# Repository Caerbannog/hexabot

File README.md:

Hexabot Sources
===============

Design files and source code of a mobile robot for the [Eurobot competition](http://www.eurobot.org/).

The controller board is built in [KiCad](http://www.kicad.org/)
around a [dsPIC33EP256MU806](https://www.microchip.com/products/dsPIC33EP256MU806) (QFN, motor control, USB).
You can control it from your development machine or an embedded Linux like the Raspberry Pi (raspbian jessie recommended).

Controller PCB
--------------
The board handles various functions: motor control, odometry, sensors and servomotors.
It has two layers, 10cm*10cm and mostly 0806 SMT components.

You can buy 10 PCBs for 32$ at [SeeedStudio](http://www.seeedstudio.com/service/index.php?r=pcb).
Then we hand-soldered ours.

Embedded Software
-----------------
The source code for the microcontroller is in [hexabot-dsPIC33.X](hexabot-dsPIC33.X/).
It is controlled with the tools in [linux](linux/). Most are Python scripts that
use [PyUSB](https://walac.github.io/pyusb/) to communicate with the board through independant USB endpoints:
- Bulk commands to set parameters and read back values. The basic idea is to run `./command.py <register> <value>` to set a value.
- Bulk metrics broadcasting, isochronous packets for time-sensitive data. Dump them with `./usb_controller.py`.
- Serial port for debugging. Show the debug console with `miniterm.py /dev/ttyACM* 9600 -D`.

A higher level scripts like `joystick.py` uses the command endpoint to let you control the motors with a USB joystick.

User Interface
--------------
The [ui](ui/) directory contains a Python webserver with these features:
- live updates of the position according to odometry,
- graphs to visualize metrics,
- maybe someday a way to send commands.

Setup
-----
Download and install the [MPLABX IDE](http://www.microchip.com/mplabx/) and the [XC16 compiler](http://www.microchip.com/compilers/).
You need xc16 v1.25+ because of bug XC16-781 (snprintf).
Sadly the peripheral libraries were last shipped with v1.24 and the new Code Configurator doesn't support dsPIC33E yet.
You need to copy the libraries from one installed version to the other.

Install Python 3 and debugging tools like Wireshark.
For Ubuntu 15.04 you can run:
```bash
git clone https://github.com/Caerbannog/hexabot.git
sudo apt-get install python3-pip wireshark
sudo pip3 install pyusb==1.0.0b1 autobahn==0.10.4 pyinotify==0.9.6 bottle==0.12.8 pyserial
sudo adduser $USER dialout
sudo adduser $USER wireshark
echo usbmon | sudo tee -a /etc/modules
sudo cp 99-hexabot.rules /etc/udev/rules.d/
sudo service udev reload # then you need to replug the device
```

Contributing
------------
Pull requests are welcome on the project page:
<https://github.com/Caerbannog/hexabot>

Licenses
--------
- Hardware design files are published under the CERN OHL v.1.2.
- Source code is published under the GPLv3 or later.
- Note that Microchip's USB library and the CDC-basic demo have a more restrictive license.

TODO list
---------
- Documentation for the code. Links to documentation for the motor control and odometry.

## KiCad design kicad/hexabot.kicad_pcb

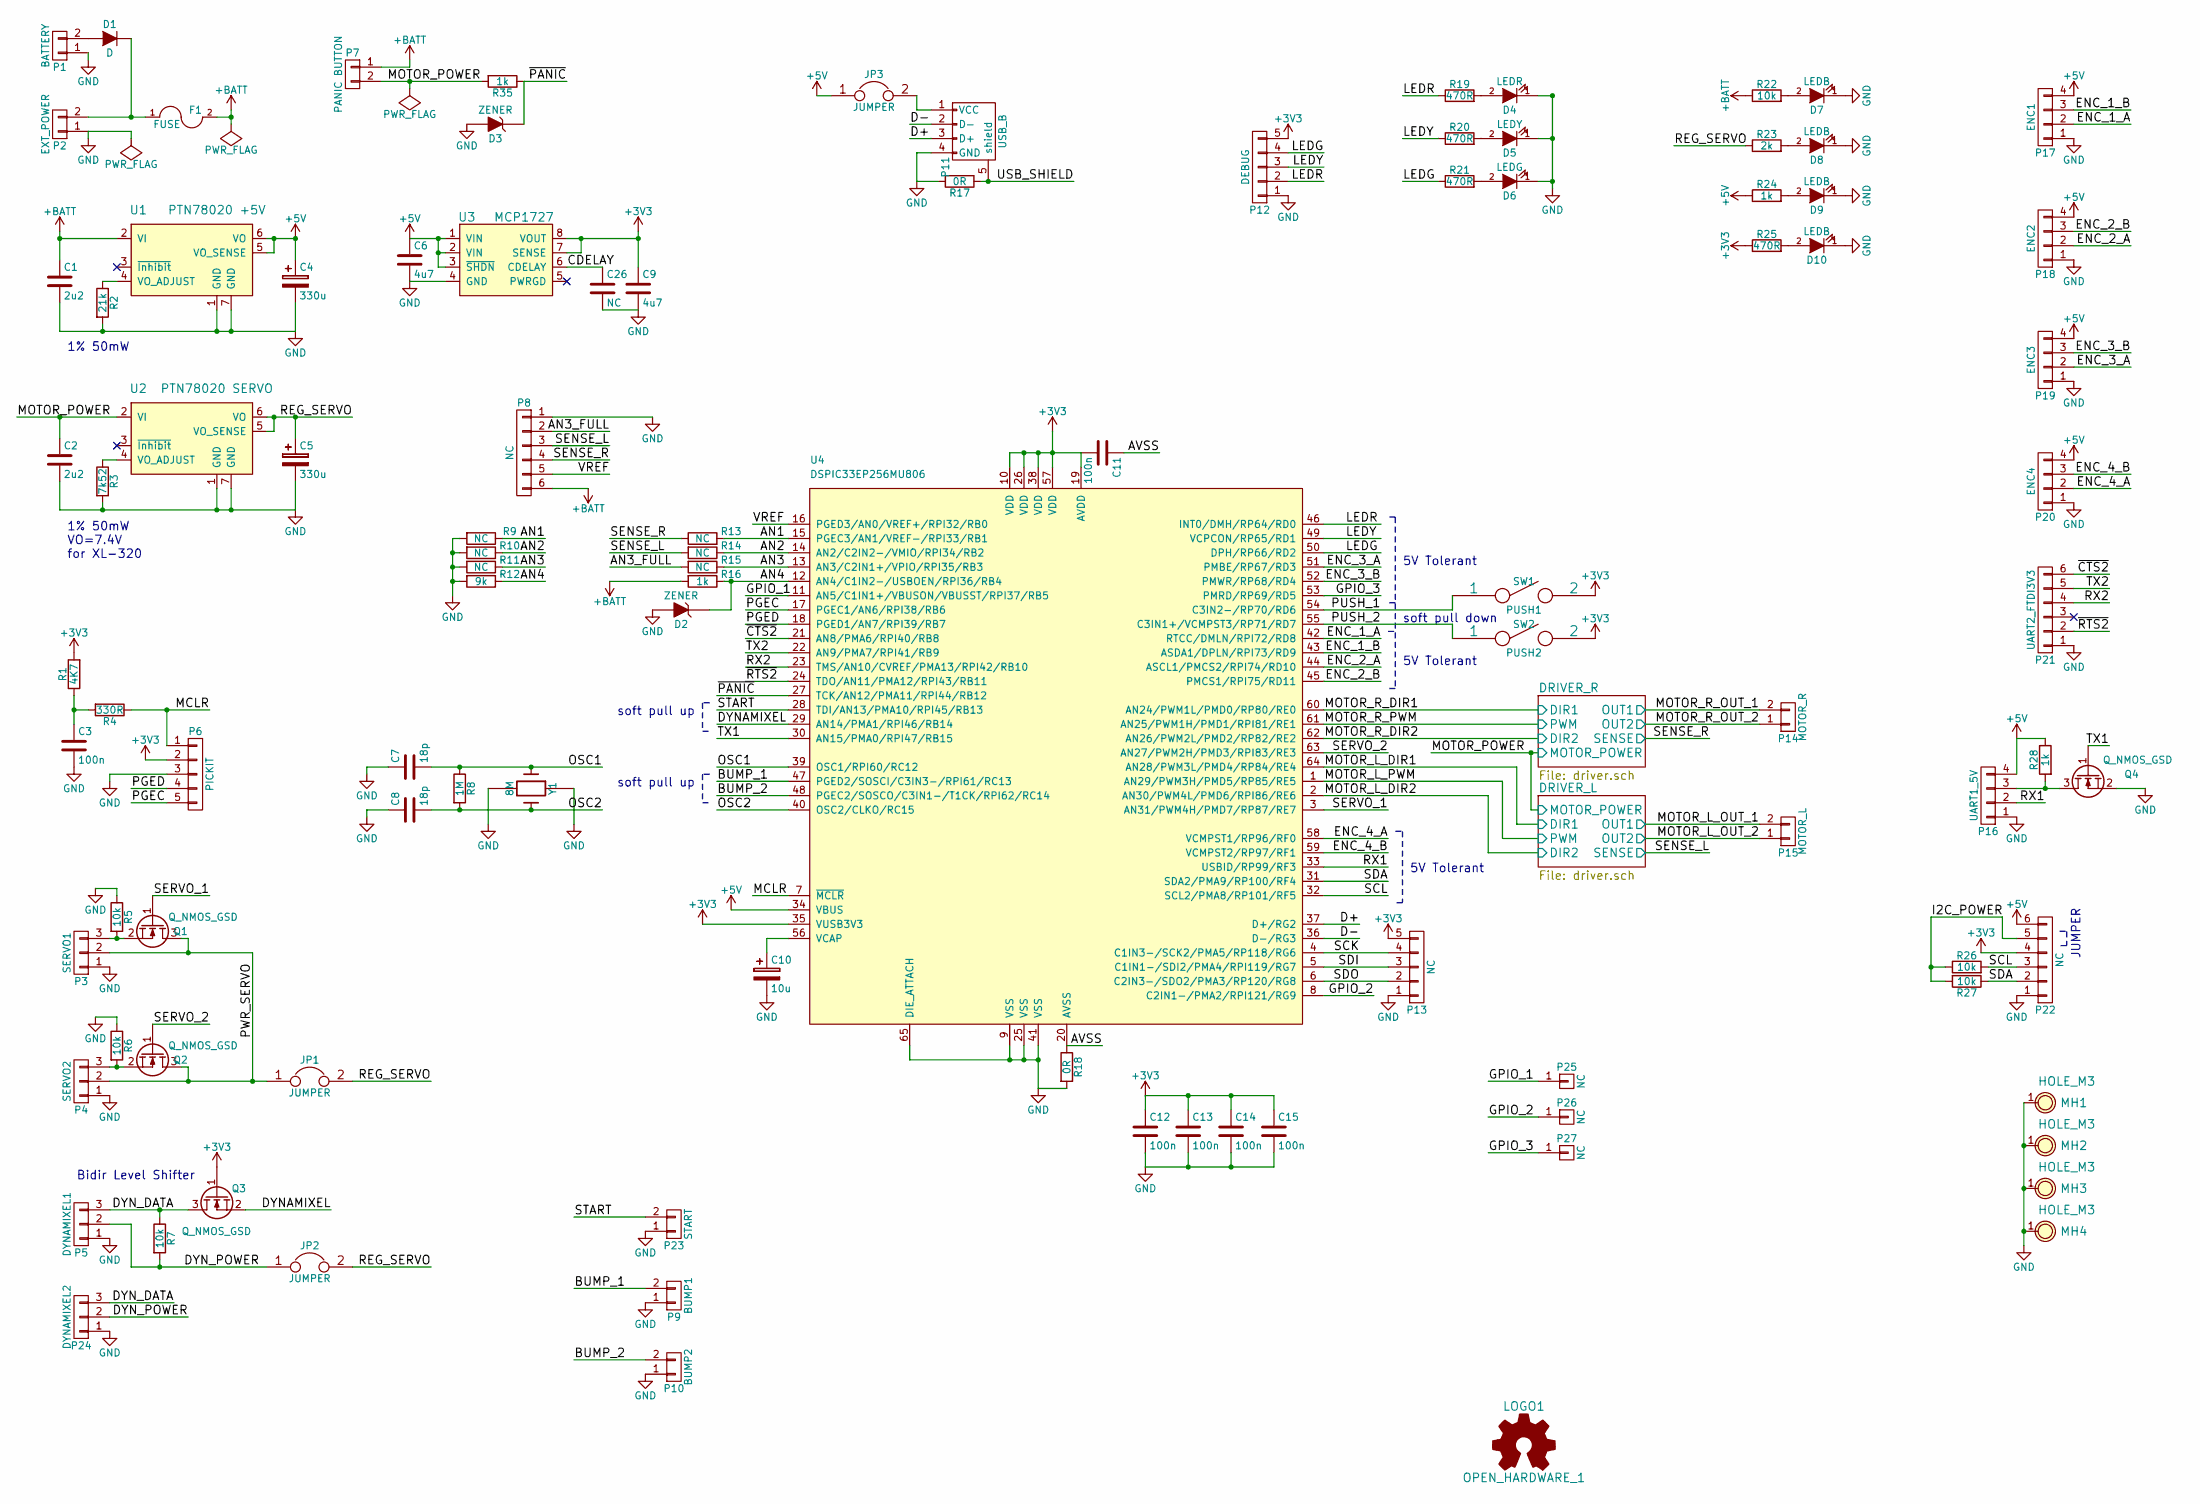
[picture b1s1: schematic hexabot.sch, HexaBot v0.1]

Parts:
C1, C2: 2u2; R_0805
C3, C11, C12, C13, C14, C15: 100n; R_0805
C4: 330u; c_elec_8x10.5
C5: 330u; c_elec_10x10.5
C6, C9: 4u7; R_0805
C7, C8: 18p; R_0805
C10: 10u; R_0805
C26: NC; R_0805
D1: D; SOD-128
D2, D3: ZENER; SOD-323
D4: LEDR; R_0805
D5: LEDY; R_0805
D6: LEDG; R_0805
D7, D8, D9, D10: LEDB; R_0805
F1: FUSE; R_1206_HandSoldering
JP1, JP2, JP3: JUMPER; Pin_Header_Straight_1x02
LOGO1: OPEN_HARDWARE_1; Symbol_OSHW-Logo_SilkScreen
MH1, MH2, MH3, MH4: HOLE_M3; M3-hole-plated
P1: BATTERY; Socket_MOLEX-KK-RM3-96mm_Lock_2pin_straight
P2: EXT_POWER; Socket_MOLEX-KK-RM3-96mm_Lock_2pin_straight
P3: SERVO1; Pin_Header_Straight_1x03
P4: SERVO2; Pin_Header_Straight_1x03
P5: DYNAMIXEL1; molex-22-03-5035
P6: PICKIT; Pin_Header_Straight_1x05
P7: PANIC BUTTON; Socket_MOLEX-KK-RM3-96mm_Lock_2pin_straight
P8: NC; Pin_Header_Straight_1x06
P9: BUMP1; Socket_MOLEX-KK-RM2-54mm_Lock_2pin_straight
P10: BUMP2; Socket_MOLEX-KK-RM2-54mm_Lock_2pin_straight
P11: USB_B; MICRO-B_USB
P12: DEBUG; Socket_MOLEX-KK-RM2-54mm_Lock_5pin_straight
P13: NC; Socket_MOLEX-KK-RM2-54mm_Lock_5pin_straight
P14: MOTOR_R; Socket_MOLEX-KK-RM3-96mm_Lock_2pin_straight
P15: MOTOR_L; Socket_MOLEX-KK-RM3-96mm_Lock_2pin_straight
P16: UART1_5V; Socket_MOLEX-KK-RM2-54mm_Lock_4pin_straight
P17: ENC1; Socket_MOLEX-KK-RM2-54mm_Lock_4pin_straight
P18: ENC2; Socket_MOLEX-KK-RM2-54mm_Lock_4pin_straight
P19: ENC3; Socket_MOLEX-KK-RM2-54mm_Lock_4pin_straight
P20: ENC4; Socket_MOLEX-KK-RM2-54mm_Lock_4pin_straight
P21: UART2_FTDI3V3; Pin_Header_Straight_1x06
P22: NC; Socket_MOLEX-KK-RM2-54mm_Lock_6pin_straight
P23: START; Socket_MOLEX-KK-RM2-54mm_Lock_2pin_straight
P24: DYNAMIXEL2; molex-22-03-5035
P25, P26, P27: NC; Pin_Header_Straight_1x01
Q1, Q2, Q3, Q4: Q_NMOS_GSD; SOT-23
R1: 4K7; R_0805
R2: 21k; R_0805
R3: 7k52; R_0805
R4: 330R; R_0805
R5, R6, R7, R22, R26, R27: 10k; R_0805
R8: 1M; R_0805
R9, R10, R11, R13, R14, R15: NC; R_0805
R12: 9k; R_0805
R16, R24, R28, R35: 1k; R_0805
R17, R18: 0R; R_0805
R19, R20, R21, R25: 470R; R_0805
R23: 2k; R_0805
SW1: PUSH1; SW_PUSH-SMD
SW2: PUSH2; SW_PUSH-SMD
U1: PTN78020 +5V; PTN78020H
U2: PTN78020 SERVO; PTN78020H
U3: MCP1727; SOIC-8_3.9x4.9mm_Pitch1.27mm
U4: DSPIC33EP256MU806; QFN-64-1EP_9x9mm_Pitch0.5mm
Y1: 8M; XTAL_5x3.2

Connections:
+3V3: C9.1, C11.2, C12.1, C13.1, C14.1, C15.1, P6.2, P12.5, P13.5, P22.4, Q3.1 (G), R1.2, R25.1, SW1.2, SW2.2, U3.7 (SENSE), U3.8 (VOUT), U4.10 (VDD), U4.19 (AVDD), U4.26 (VDD), U4.35 (VUSB3V3), U4.38 (VDD), U4.57 (VDD)
+5V: C4.1, C6.1, JP3.1, P16.4, P17.4, P18.4, P19.4, P20.4, P22.6, R24.1, R28.1, U1.5 (VO_SENSE), U1.6 (VO), U3.1 (VIN), U3.2 (VIN), U3.3 (~SHDN), U4.34 (VBUS)
+BATT: C1.1, F1.2, P7.1, P8.6, R16.2, R22.1, U1.2 (VI)
/AN1: R9.1, R13.2, U4.15 (PGEC3/AN1/VREF-/RPI33/RB1)
/AN2: R10.1, R14.1, U4.14 (AN2/C2IN2-/VMIO/RPI34/RB2)
/AN3: R11.1, R15.1, U4.13 (AN3/C2IN1+/VPIO/RPI35/RB3)
/AN3_FULL: P8.2, R15.2
/AN4: D2.1 (K), R12.1, R16.1, U4.12 (AN4/C1IN2-/USBOEN/RPI36/RB4)
/AVSS: C11.1, R18.1, U4.20 (AVSS)
/BUMP_1: P9.2, U4.47 (PGED2/SOSCI/C3IN3-/RPI61/RC13)
/BUMP_2: P10.2, U4.48 (PGEC2/SOSCO/C3IN1-/T1CK/RPI62/RC14)
/CDELAY: C26.1, U3.6 (CDELAY)
/D+: P11.3 (D+), U4.37 (D+/RG2)
/D-: P11.2 (D-), U4.36 (D-/RG3)
/DRIVER_L/DIR1: U4.64 (AN28/PWM3L/PMD4/RP84/RE4); also elsewhere on the board
/DRIVER_L/DIR2: U4.2 (AN30/PWM4L/PMD6/RPI86/RE6); also elsewhere on the board
/DRIVER_L/MOTOR_POWER: C2.1, P7.2, R35.2, U2.2 (VI); also elsewhere on the board
/DRIVER_L/OUT1: P15.2; also elsewhere on the board
/DRIVER_L/OUT2: P15.1; also elsewhere on the board
/DRIVER_L/PWM: U4.1 (AN29/PWM3H/PMD5/RP85/RE5); also elsewhere on the board
/DRIVER_L/SENSE: P8.3, R14.2; also elsewhere on the board
/DRIVER_R/DIR1: U4.60 (AN24/PWM1L/PMD0/RP80/RE0); also elsewhere on the board
/DRIVER_R/DIR2: U4.62 (AN26/PWM2L/PMD2/RP82/RE2); also elsewhere on the board
/DRIVER_R/OUT1: P14.2; also elsewhere on the board
/DRIVER_R/OUT2: P14.1; also elsewhere on the board
/DRIVER_R/PWM: U4.61 (AN25/PWM1H/PMD1/RPI81/RE1); also elsewhere on the board
/DRIVER_R/SENSE: P8.4, R13.1; also elsewhere on the board
/DYNAMIXEL: Q3.2 (S), U4.29 (AN14/PMA1/RPI46/RB14)
/DYN_DATA: P5.3, P24.3, Q3.3 (D), R7.1
/DYN_POWER: JP2.1, P5.2, P24.2, R7.2
/ENC_1_A: P17.2, U4.42 (RTCC/DMLN/RPI72/RD8)
/ENC_1_B: P17.3, U4.43 (ASDA1/DPLN/RPI73/RD9)
/ENC_2_A: P18.2, U4.44 (ASCL1/PMCS2/RPI74/RD10)
/ENC_2_B: P18.3, U4.45 (PMCS1/RPI75/RD11)
/ENC_3_A: P19.2, U4.51 (PMBE/RP67/RD3)
/ENC_3_B: P19.3, U4.52 (PMWR/RP68/RD4)
/ENC_4_A: P20.2, U4.58 (VCMPST1/RP96/RF0)
/ENC_4_B: P20.3, U4.59 (VCMPST2/RP97/RF1)
/GPIO_1: P25.1, U4.11 (AN5/C1IN1+/VBUSON/VBUSST/RPI37/RB5)
/GPIO_2: P26.1, U4.8 (C2IN1-/PMA2/RPI121/RG9)
/GPIO_3: P27.1, U4.53 (PMRD/RP69/RD5)
/I2C_POWER: P22.5, R26.1, R27.2
/LEDG: P12.4, R21.1, U4.50 (DPH/RP66/RD2)
/LEDR: P12.2, R19.1, U4.46 (INT0/DMH/RP64/RD0)
/LEDY: P12.3, R20.1, U4.49 (VCPCON/RP65/RD1)
/MCLR: P6.1, R4.1, U4.7 (~MCLR)
/OSC1: C7.2, R8.1, U4.39 (OSC1/RPI60/RC12), Y1.1
/OSC2: C8.2, R8.2, U4.40 (OSC2/CLKO/RC15), Y1.2
/PGEC: P6.5, U4.17 (PGEC1/AN6/RPI38/RB6)
/PGED: P6.4, U4.18 (PGED1/AN7/RPI39/RB7)
/PUSH_1: SW1.1, U4.54 (C3IN2-/RP70/RD6)
/PUSH_2: SW2.1, U4.55 (C3IN1+/VCMPST3/RP71/RD7)
/PWR_SERVO: JP1.1, P3.2, P4.2, Q1.3 (D), Q2.3 (D)
/REG_SERVO: C5.1, JP1.2, JP2.2, R23.1, U2.5 (VO_SENSE), U2.6 (VO)
/RX1: P16.2, U4.33 (USBID/RP99/RF3)
/RX2: P21.4, U4.23 (TMS/AN10/CVREF/PMA13/RPI42/RB10)
/SCK: P13.4, U4.4 (C1IN3-/SCK2/PMA5/RP118/RG6)
/SCL: P22.3, R26.2, U4.32 (SCL2/PMA8/RP101/RF5)
/SDA: P22.2, R27.1, U4.31 (SDA2/PMA9/RP100/RF4)
/SDI: P13.3, U4.5 (C1IN1-/SDI2/PMA4/RPI119/RG7)
/SDO: P13.2, U4.6 (C2IN3-/SDO2/PMA3/RP120/RG8)
/SERVO_1: Q1.1 (G), U4.3 (AN31/PWM4H/PMD7/RP87/RE7)
/SERVO_2: Q2.1 (G), U4.63 (AN27/PWM2H/PMD3/RPI83/RE3)
/START: P23.2, U4.28 (TDI/AN13/PMA10/RPI45/RB13)
/TX1: Q4.1 (G), U4.30 (AN15/PMA0/RPI47/RB15)
/TX2: P21.5, U4.22 (AN9/PMA7/RPI41/RB9)
/USB_SHIELD: P11.5 (shield), R17.1
/VREF: P8.5, U4.16 (PGED3/AN0/VREF+/RPI32/RB0)
/~CTS2: P21.6, U4.21 (AN8/PMA6/RPI40/RB8)
/~PANIC: D3.1 (K), R35.1, U4.27 (TCK/AN12/PMA11/RPI44/RB12)
/~RTS2: P21.2, U4.24 (TDO/AN11/PMA12/RPI43/RB11)
GND: C1.2, C2.2, C3.2, C4.2, C5.2, C6.2, C7.1, C8.1, C9.2, C10.2, C12.2, C13.2, C14.2, C15.2, C26.2, D2.2 (A), D3.2 (A), D4.1 (K), D5.1 (K), D6.1 (K), D7.1 (K), D8.1 (K), D9.1 (K), D10.1 (K), MH1.1, MH2.1, MH3.1, MH4.1, P1.1, P2.1, P3.1, P4.1, P5.1, P6.3, P8.1, P9.1, P10.1, P11.4 (GND), P12.1, P13.1, P16.1, P17.1, P18.1, P19.1, P20.1, P21.1, P22.1, P23.1, P24.1, Q4.2 (S), R2.2, R3.2, R5.1, R6.1, R9.2, R10.2, R11.2, R12.2, R17.2, R18.2, U1.1 (GND), U1.7 (GND), U2.1 (GND), U2.7 (GND), U3.4 (GND), U4.9 (VSS), U4.25 (VSS), U4.41 (VSS), U4.65 (DIE_ATTACH), Y1.3 (GND), Y1.4 (GND); also elsewhere on the board
unnamed: C3.1, R1.1, R4.2
unnamed: C10.1, U4.56 (VCAP)
unnamed: D1.1 (K), F1.1, P2.2
unnamed: D1.2 (A), P1.2
unnamed: D4.2 (A), R19.2
unnamed: D5.2 (A), R20.2
unnamed: D6.2 (A), R21.2
unnamed: D7.2 (A), R22.2
unnamed: D8.2 (A), R23.2
unnamed: D9.2 (A), R24.2
unnamed: D10.2 (A), R25.2
unnamed: JP3.2, P11.1 (VCC)
unnamed: P3.3, Q1.2 (S), R5.2
unnamed: P4.3, Q2.2 (S), R6.2
unnamed: P16.3, Q4.3 (D), R28.2
unnamed: R2.1, U1.4 (VO_ADJUST)
unnamed: R3.1, U2.4 (VO_ADJUST)

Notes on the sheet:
5V Tolerant
1% 50mW
1% 50mW VO=7.4V for XL-320
soft pull down
JUMPER
soft pull up
Bidir Level Shifter

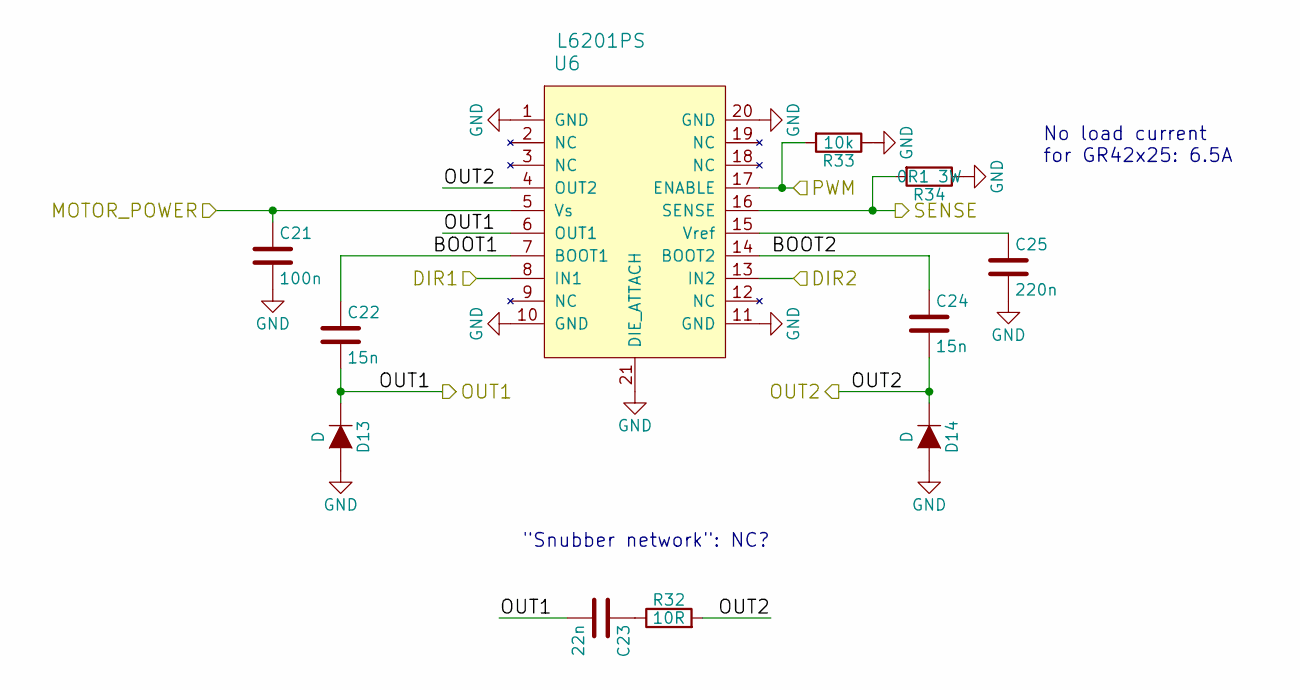
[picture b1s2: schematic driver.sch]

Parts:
C16: 100n; R_0805
C17, C19: 15n; R_0805
C18: 22n; R_0805
C20: 220n; R_0805
D11, D12: D; SOD-123
R29: 10R; R_0805
R30: 10k; R_0805
R31: 0R1 3W; R_1206
U5: L6201PS; powerso-20

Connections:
/DRIVER_L/MOTOR_POWER: C16.1, U5.5 (Vs); also elsewhere on the board
/DRIVER_R/BOOT1: C17.1, U5.7 (BOOT1)
/DRIVER_R/BOOT2: C19.1, U5.14 (BOOT2)
/DRIVER_R/DIR1: U5.8 (IN1); also elsewhere on the board
/DRIVER_R/DIR2: U5.13 (IN2); also elsewhere on the board
/DRIVER_R/OUT1: C17.2, C18.2, D11.1 (K), U5.6 (OUT1); also elsewhere on the board
/DRIVER_R/OUT2: C19.2, D12.1 (K), R29.2, U5.4 (OUT2); also elsewhere on the board
/DRIVER_R/PWM: R30.2, U5.17 (ENABLE); also elsewhere on the board
/DRIVER_R/SENSE: R31.2, U5.16 (SENSE); also elsewhere on the board
GND: C16.2, C20.2, D11.2 (A), D12.2 (A), R30.1, R31.1, U5.1 (GND), U5.10 (GND), U5.11 (GND), U5.20 (GND), U5.21 (DIE_ATTACH); also elsewhere on the board
unnamed: C18.1, R29.1
unnamed: C20.1, U5.15 (Vref)

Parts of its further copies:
C21: 100n; R_0805
C22, C24: 15n; R_0805
C23: 22n; R_0805
C25: 220n; R_0805
D13, D14: D; SOD-123
R32: 10R; R_0805
R33: 10k; R_0805
R34: 0R1 3W; R_1206
U6: L6201PS; powerso-20

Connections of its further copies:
/DRIVER_L/BOOT1: C22.1, U6.7 (BOOT1)
/DRIVER_L/BOOT2: C24.1, U6.14 (BOOT2)
/DRIVER_L/DIR1: U6.8 (IN1); also elsewhere on the board
/DRIVER_L/DIR2: U6.13 (IN2); also elsewhere on the board
/DRIVER_L/MOTOR_POWER: C21.1, U6.5 (Vs); also elsewhere on the board
/DRIVER_L/OUT1: C22.2, C23.2, D13.1 (K), U6.6 (OUT1); also elsewhere on the board
/DRIVER_L/OUT2: C24.2, D14.1 (K), R32.2, U6.4 (OUT2); also elsewhere on the board
/DRIVER_L/PWM: R33.2, U6.17 (ENABLE); also elsewhere on the board
/DRIVER_L/SENSE: R34.2, U6.16 (SENSE); also elsewhere on the board
GND: C21.2, C25.2, D13.2 (A), D14.2 (A), R33.1, R34.1, U6.1 (GND), U6.10 (GND), U6.11 (GND), U6.20 (GND), U6.21 (DIE_ATTACH); also elsewhere on the board
unnamed: C23.1, R32.1
unnamed: C25.1, U6.15 (Vref)

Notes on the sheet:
"Snubber network": NC?
No load current for GR42x25: 6.5A

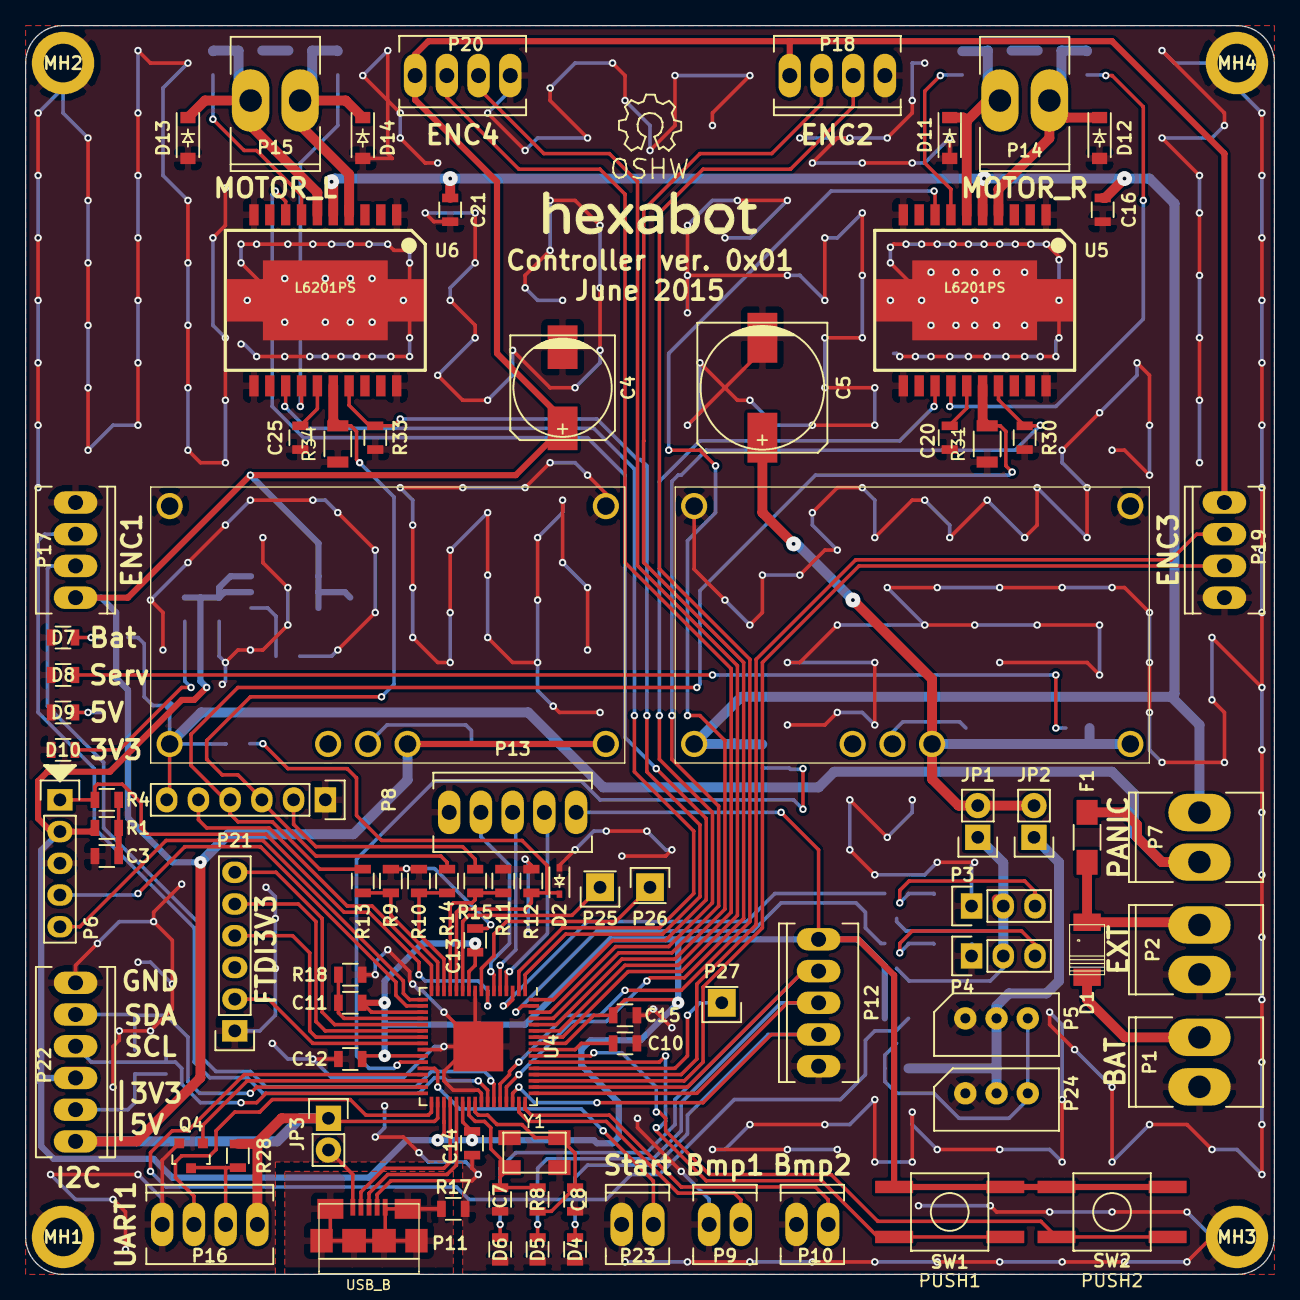
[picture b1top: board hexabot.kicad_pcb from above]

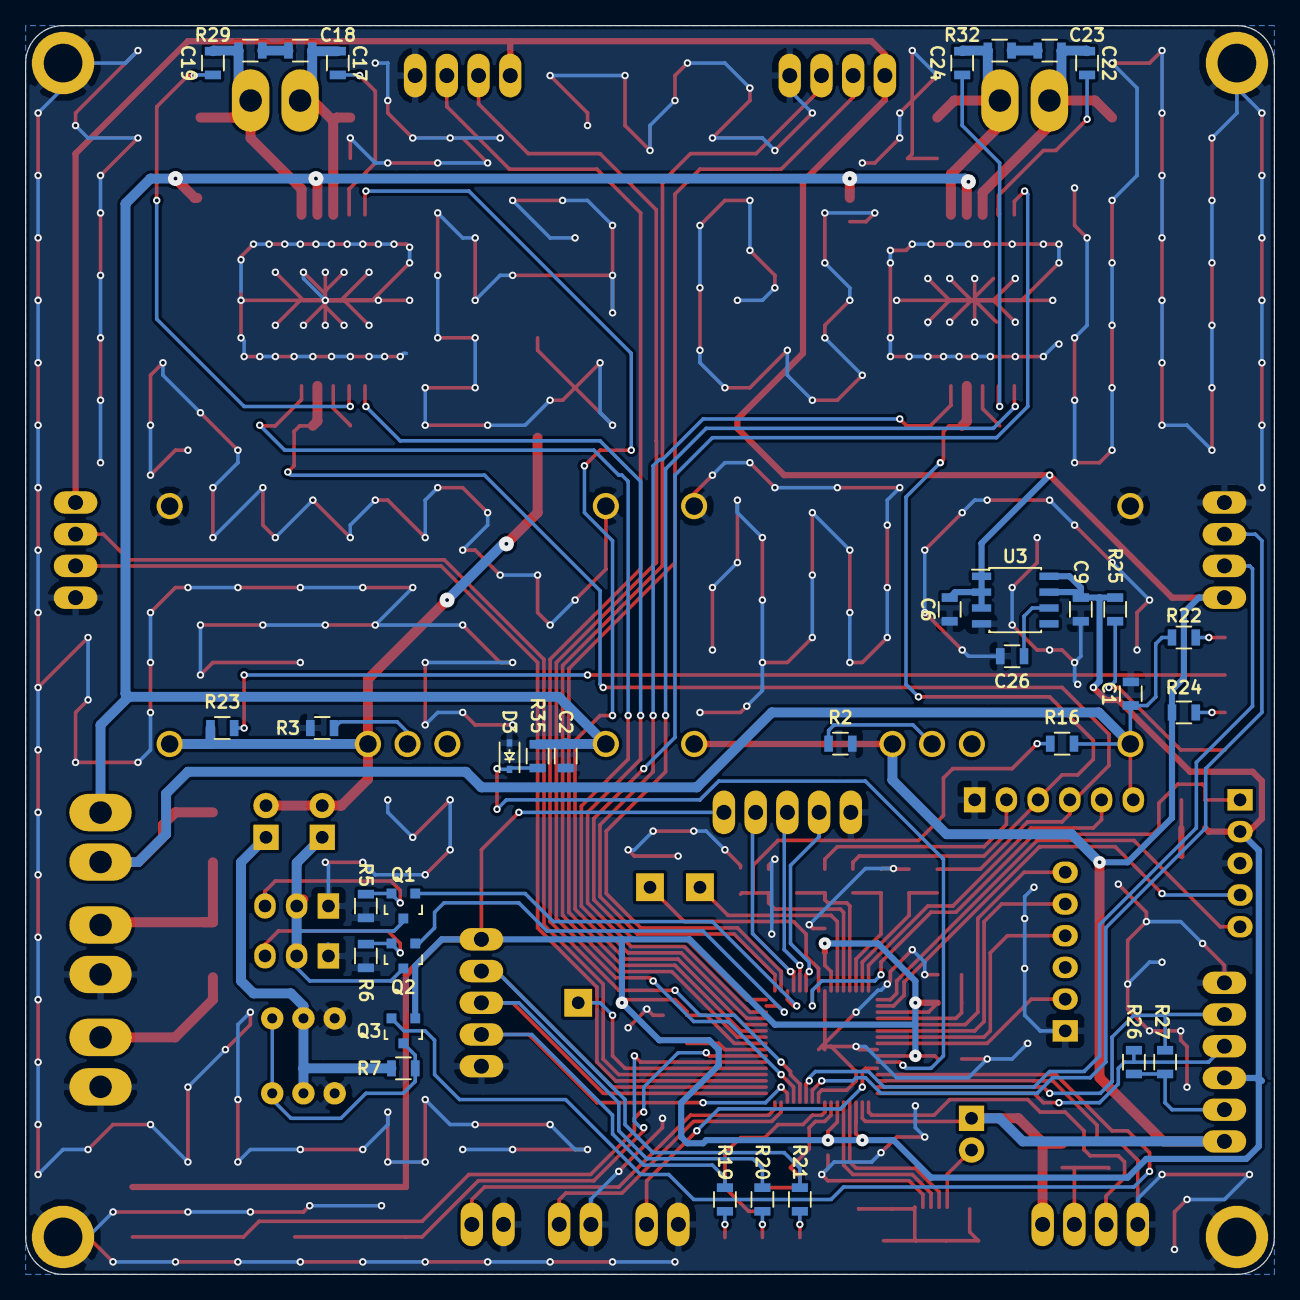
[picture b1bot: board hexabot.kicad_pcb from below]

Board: 2 copper layers, 100.0 x 100.0 mm, 124 parts (34 on the bottom side), 97 nets.

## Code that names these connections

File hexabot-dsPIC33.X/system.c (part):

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
// FOSC
#pragma config POSCMD = HS              // Primary Oscillator Mode Select bits (HS Crystal Oscillator Mode)
#pragma config OSCIOFNC = ON            // OSC2 Pin Function bit (OSC2 is general purpose digital I/O pin)
#pragma config IOL1WAY = OFF            // Peripheral pin select configuration (Allow multiple reconfigurations)
#pragma config FCKSM = CSDCMD           // Clock Switching Mode bits (Both Clock switching and Fail-safe Clock Monitor are disabled)

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                    & OC_OUT_NOT_INVERT & OC_CASCADE_DISABLE & OC_SYNC_ENABLE
                    & OC_TRIGGER_TIMER & OC_DIRN_OUTPUT & OC_SYNC_TRIG_IN_TMR5,
                    0, 0);
            PPSOutput(OUT_FN_PPS_OC3, OUT_PIN_PPS_RP87); // SERVO_1
            OpenOC4(OC_IDLE_STOP & OC_TIMER5_SRC & OC_FAULTA_IN_DISABLE & OC_FAULTB_IN_DISABLE
                    & OC_FAULTC_IN_DISABLE & 0xff8f & OC_TRIG_CLEAR_SYNC & OC_PWM_EDGE_ALIGN,
                    OC_FAULT_MODE_PWM_CYCLE & OC_PWM_FAULT_OUT_LOW & (~OC_FAULT_PIN_OUT)
                    & OC_OUT_NOT_INVERT & OC_CASCADE_DISABLE & OC_SYNC_ENABLE
                    & OC_TRIGGER_TIMER & OC_DIRN_OUTPUT & OC_SYNC_TRIG_IN_TMR5,
                    0, 0); // Same config.
            // HW FIXME: pin SERVO_2
            
            break;

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
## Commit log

2015-06-06 Add layout and schematics, update README, change iso
2015-06-06 Compute time for metrics
2015-06-07 Create project and schematic for dsPIC
2015-06-07 Cleanup paths
2015-06-07 Add L6201PS
2015-06-08 Add modules
2015-06-09 Start schematic
2015-06-09 More components
2015-06-09 More sch
2015-06-10 Subsheet for drivers
2015-06-10 PIC datasheet added Footprint library created
2015-06-10 Most of sch ready
2015-06-10 Add fp-lib-table
2015-06-11 Probably ready for layout
2015-06-11 Partial footprint association
2015-06-11 Remove KK for motors
2015-06-13 few modules added, placement started
2015-06-13 Add footprint for AX-12 connector
2015-06-13 First draft layout. To optimize to 10*10cm
2015-06-14 Draft layout with files
2015-06-14 Add hexabot draft logo
2015-06-14 Add new crystal footprint
2015-06-14 Layout nearly done, ground plane to check, missing connections, change quartz footprint
2015-06-15 Layout done, check to do, logo to add
2015-06-15 Layout done. Print test to do.
2015-06-22 Few modifs on silk screen gerber generated
2015-06-23 Rsense footprintf modified. Anular ring adjusted. Ready to order
2015-06-27 SeeedFusionPCB order files v1
2015-06-27 Move previous files to kicad/, add CDC demo for dspic33E in a single dir
2015-06-27 Remove virtual folder, change manufacturer
2015-06-29 New descriptors accepted by Linux, CDC still works
2015-06-29 The first command should work soon.
2015-07-01 Add bidirectionnal control commands
2015-07-02 Add command parsing
2015-07-03 Commands work in both directions, the header changed
2015-07-04 Add hexabot.rules and update README
2015-07-05 Move things around, add licenses
2015-07-05 Start adding metrics
2015-07-05 Cleanup permissions and include
2015-07-05 Add .gitignore for python
2015-07-05 Fix endpoint direction that prevented USB configuration
2015-07-05 Metrics reception works, minus the 'time' field
2015-07-05 Move isochronous do dedicated interface, add boilerplate
2015-07-06 Received data from the isochronous endpoint, nothing to brag about
2015-07-06 Add timer
2015-07-11 Add some 3D packages
2015-07-15 Blinking the board works. Approx 1 Hz with FRC.
2015-07-16 Hexabot controller ver 0x01 sucessfully enumerated
2015-07-16 Add BOM for v1
2015-07-16 First success with registers
2015-07-19 First draft of peripheral configuration
2015-07-22 Fix silkscreen ENC3 => ENC4
2015-07-22 Servo and ENC1-4 work, remove some debug code
2015-07-22 Fix servo transistor in schematics, the netlist will have to change
2015-07-22 Inverse polarity of output-compare following the servo rework
2015-07-22 Swap MOTOR_R_PWM and MOTOR_R_DIR1 because of RP80, the netlist will have to change
2015-07-23 Control H bridge pins with PWM
2015-07-27 Add pullup/down, finish ADC config, fix metrics
2015-07-28 Reorganize config and registers
2015-07-28 Cleanup, duplication, fix motors
2015-07-29 Add graph UI
2015-08-04 Debug graph UI
2015-08-05 Add TODOs to improve VSENSE
2015-11-01 Add open loop joystick control
2015-11-08 Try to fix the inversion
2015-11-08 Add float commands, float motor control that works, basic speed sensing
2015-11-08 Basic PI controller on both motors
2015-11-08 Joystick control
2015-11-08 Prepare software QEI
2015-11-09 Software QEI seems to work (few errors), but would benefit from rigorous testing.
2015-11-09 Tested the different encoder combinations. TODO: use the HW QEI to validate the SW QEI.
2015-11-09 Untested odometry
2015-11-10 Basic odometry with html display
2015-11-10 Add SVG from https://github.com/roboterclubaachen/eurobot-resources/
2015-11-11 Remove iter_unpack for python 3.2, throttle joystick events
2015-11-11 Updated README, cleaner svg ui, improve odometry, more outputs for commands
2015-11-12 Rename graph to ui, use canvas
2015-11-12 Add bootstrap
2015-11-12 Add tabs
2015-11-12 Add remote procedures
2015-11-14 Change app_led_usb_status, stop motors on USB disconnect
2015-11-14 Little fixes
2015-11-14 Comment CDC test
2015-11-14 Finally traced the CDC corruption back to XC16-781 bug
2015-11-14 Don't cut in the middle of dropped lines
2015-11-14 Rename dsPIC
2015-11-14 Rename usb_controller.py
2015-11-14 Set permissions in udev rule
2015-11-14 Convert joystick to python3, crash on disconnect, Ui server listens on all interfaces
2015-11-14 Reduce PWM noise, simpler speed decoding, clean dependencies
2015-11-19 WIP: Try to implement polar control with external encoder feedback. More work is needed.
2015-11-19 Add submodule for polar-control
2021-11-07 Update to official link
    See https://forum.kicad.info/t/warning-avoid-all-links-to-kicad-pcb-org-use-kicad-org/31521/
